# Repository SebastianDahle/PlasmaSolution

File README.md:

View this project on [CADLAB.io](https://cadlab.io/project/22637). 

# PlasmaSolution

The project *PlasmaSolution* is a Marie Sklodowoska Curie Actions - Individual Fellowship by the European Commission that aims to implement non-thermal plasma technology at the Department of Wood Science and Technology, Biotechnical Faculty, University of Ljubljana, Slovenia. Further goal of the project is the development and testing of plasma-cured coatings for wood protection as an innovative new appraoch in coatings deposition.

The equipment and methodology developed in the PlasmaSolution project shall be made openly available to everyone interested in reproducing or applying them. Participation in the activities and further developments are more than welcome! In case of questions and remarks, please contact Sebastian Dahle via [sebastian.dahle@bf.uni-lj.si](mailto:sebastian.dahle@bf.uni-lj.si).

## WARNING

**!! Dealing with plasma involves using high voltages. Please make sure you are familiar with all safety instructions and necessary practices!**

## Overview

A working plasma setup requires two essential parts:
* A [power supply](HV_power_supplies/) that delivers the required electrical energy, these are located at [HV_power_supplies/](HV_power_supplies/).
* A [plasma reactor](Plasma_devices/) as mechanical part, where the plasma is ignited, these are located at [Plasma_devices/](Plasma_devices/)

This repository currently includes constructions for both parts, that can be combined as indicated in the following table:

| | [Plasma_devices](Plasma_devices/) | adjustable Surface Barrier Discharge | mini-SBD | mini-DBD-Jet | Gliding-Arc-Jet *(long/short)* |
|-------------------------|---:|:---:|:---:|:---:|:--------------:|
| **[HV_power_supplies](HV_power_supplies/)** | | | |
|  Zero Voltage Switching |    |  X  |  X  |  X  |  X (long)      |
|  mini-Flyback *(AC/DC)* |    |  -  |  ?  |  AC |  AC/DC (short) |
|  Cockcroft-Walton       |    |  -  |  -  |  -  |  X (short)     |

## Getting Started

* [SolidWorks](https://www.solidworks.com/) - The CAD software used for mechanical constructions.
  * All constructions are provided openly accessible as STEP and PDF files.
  * Free software is available to view exported 3D STEP files, such as [STP Viewer](https://stpviewer.com/).
  * A free trial version of SolidWorks is available via their [website](https://www.solidworks.com/solution/job-functions/students).
* [KiCad EDA](kicad-pcb.org/download/) - Open source software used to develop circuits and PCB layouts.
  * All wiring plans are exported to PDF for easy access.
  * All PCB layouts are exported to Gerber format for easy ordering.
* [MS Visio](https://products.office.com/visio/) - The flow chart software for wiring plans.
  * All wiring plans are provided openly accessible as SVG and PDF files.
  * A free viewer for original proprietory files is availabe from [Microsoft](https://www.microsoft.com/download/details.aspx?id=35811).
* [MS Excel](https://products.office.com/excel/) - Used for tables and lists, whenever markdown files are less suited.
  * All charts, tables, and lists are exported as CSV and PDF.
* [MS Word](https://products.office.com/word/) - Used for instructions and publications, whenever markdown files are less suited.
  * All documents are exported to PDF.

## Contributing

Please read [CONTRIBUTING.md](https://github.com/SebastianDahle/PlasmaSolution/blob/master/CONTRIBUTING.md) for details on how to participate and the process for submitting pull requests to us, and check [CODE_OF_CONDUCT.md](https://github.com/SebastianDahle/PlasmaSolution/blob/master/CODE_OF_CONDUCT.md) for our code of conduct.

All releases are uploaded to Zenodo. 
* Latest release v1.0.0, see: 
* *Cite release as:* Sebastian Dahle. (2019, April 22). SebastianDahle/PlasmaSolution: First release (Version 1.0.0). Zenodo. http://doi.org/10.5281/zenodo.2648790

## Versioning

We use [SemVer](http://semver.org/) for versioning. For the versions available, see the [tags on this repository](https://github.com/SebastianDahle/PlasmaSolution/tags). 

## Authors

* **Billie Thompson** - *Initial work: README.md template* - [PurpleBooth](https://github.com/PurpleBooth)
* **Sebastian Dahle** - *Project coordinator & fellow PlasmaSolution* - [SebastianDahle](https://github.com/SebastianDahle)

See also the list of [contributors](https://github.com/SebastianDahle/PlasmaSolution/contributors) who participated in this project.

## License

This project is licensed under the GNU General Public License - see the [LICENSE.md](https://github.com/SebastianDahle/PlasmaSolution/blob/master/LICENSE) file for details

## Acknowledgments

* The project PlasmaSolution has received funding from the European Union's Horizon 2020 research and innovation programme under grant agreement No 745936.

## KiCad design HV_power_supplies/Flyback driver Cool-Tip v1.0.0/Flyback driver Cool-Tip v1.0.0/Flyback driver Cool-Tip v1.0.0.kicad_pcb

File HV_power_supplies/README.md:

# HV power supplies for plasma applications

## WARNING

**!! Manipulation of high voltages includes sincere health risks. Please make sure you are familiar with all safety instructions and necessary practices!**

## Overview

The following table provides an overview on the available constructions including basic properties:

| HV Power Supply        | Type | peak Voltage    | peak Power | Comments |
|------------------------|:----:|-----------------|-----------:|----------|
| Zero Voltage Switching |  AC  |  15 kV max      |  300 W max | USB+BT controlled; internal oscilloscope |
| mini-Flyback           |  AC  |  15 kV max      |   70 W max | Cheap & simple |
|                        |  DC  |  30 kV max      |   70 W max | Cheap & simple |
| Cockcroft-Walton       |  DC  | 2.8 kV / module |  500 W max | Easy scalable  |

## [Zero Voltage Switching](https://github.com/SebastianDahle/PlasmaSolution/tree/master/HV_power_supplies/ZVS-driver)

TODO

## [Mini-Flyback](https://github.com/SebastianDahle/PlasmaSolution/tree/master/HV_power_supplies/mini-Flyback)

*AC and DC version*

TODO

## [Cockcroft-Walton generator](https://github.com/SebastianDahle/PlasmaSolution/tree/master/HV_power_supplies/Cockcroft-Walton)

TODO

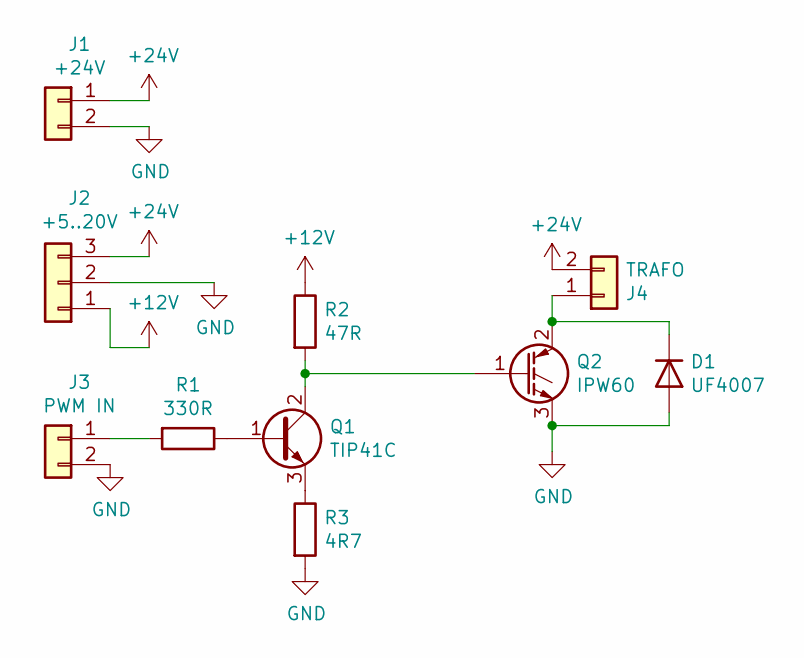
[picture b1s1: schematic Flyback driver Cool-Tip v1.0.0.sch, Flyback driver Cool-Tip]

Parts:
D1: UF4007; D_DO-201AD_P5.08mm_Vertical_AnodeUp
J1: +24V; TerminalBlock_Phoenix_MKDS-3-2-5.08_1x02_P5.08mm_Horizontal
J2: +5..20V; TerminalBlock_Phoenix_MKDS-1,5-3-5.08_1x03_P5.08mm_Horizont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
J3: PWM IN; TerminalBlock_Phoenix_MKDS-1,5-2-5.08_1x02_P5.08mm_Horizont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
J4: TRAFO; TerminalBlock_Phoenix_MKDS-3-2-5.08_1x02_P5.08mm_Horizontal
Q1: TIP41C; TO-220-3_Vertical
Q2: IPW60; TO-247-3_Vertical
R1: 330R; R_Axial_DIN0411_L9.9mm_D3.6mm_P12.70mm_Horizontal
R2: 47R; R_Axial_DIN0411_L9.9mm_D3.6mm_P12.70mm_Horizontal
R3: 4R7; R_Axial_DIN0411_L9.9mm_D3.6mm_P12.70mm_Horizontal

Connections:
+12V: J2.1, R2.1
+24V: J1.1, J2.3, J4.2
GND: D1.2 (A), J1.2, J2.2, J3.2, Q2.3 (E), R3.2
unnamed: D1.1 (K), J4.1, Q2.2 (C)
unnamed: J3.1, R1.2
unnamed: Q1.1 (B), R1.1
unnamed: Q1.2 (C), Q2.1 (G), R2.2
unnamed: Q1.3 (E), R3.1

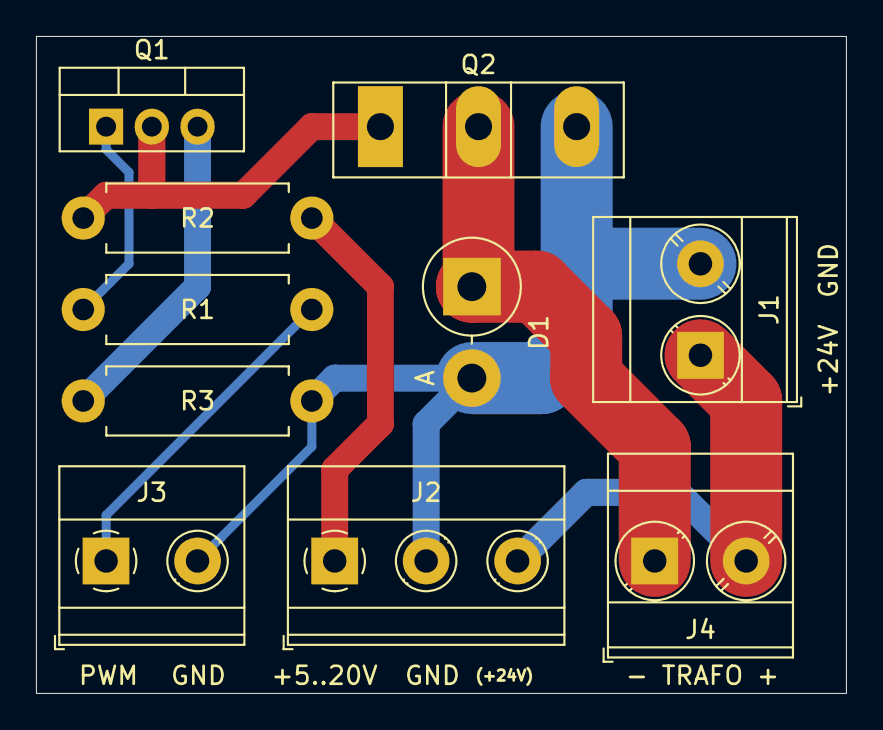
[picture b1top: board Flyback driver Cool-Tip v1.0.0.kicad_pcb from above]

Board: 2 copper layers, 45.0 x 36.5 mm, 10 parts (0 on the bottom side), 8 nets.

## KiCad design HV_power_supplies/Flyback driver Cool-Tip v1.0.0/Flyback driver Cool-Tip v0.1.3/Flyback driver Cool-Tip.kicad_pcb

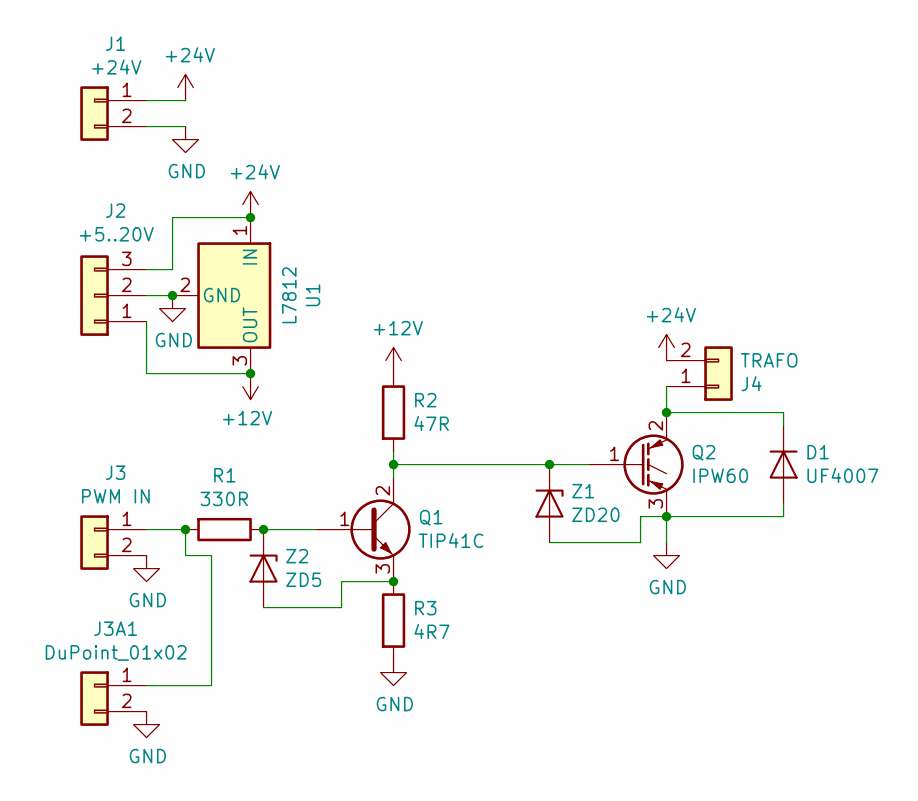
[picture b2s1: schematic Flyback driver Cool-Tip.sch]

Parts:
D1: UF4007; D_DO-201AD_P5.08mm_Vertical_AnodeUp
J1: +24V; TerminalBlock_Phoenix_MKDS-3-2-5.08_1x02_P5.08mm_Horizontal
J2: +5..20V; TerminalBlock_Phoenix_MKDS-1,5-3-5.08_1x03_P5.08mm_Horizont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
J3: PWM IN; TerminalBlock_Phoenix_MKDS-1,5-2-5.08_1x02_P5.08mm_Horizont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
J3A1: DuPoint_01x02; PinHeader_1x02_P2.54mm_Vertical
J4: TRAFO; TerminalBlock_Phoenix_MKDS-3-2-5.08_1x02_P5.08mm_Horizontal
Q1: TIP41C; TO-220-3_Vertical
Q2: IPW60; TO-247-3_Vertical
R1: 330R; R_Axial_DIN0411_L9.9mm_D3.6mm_P12.70mm_Horizontal
R2: 47R; R_Axial_DIN0411_L9.9mm_D3.6mm_P12.70mm_Horizontal
R3: 4R7; R_Axial_DIN0411_L9.9mm_D3.6mm_P12.70mm_Horizontal
U1: L7812; TO-220-3_Vertical
Z1: ZD20; D_DO-41_SOD81_P2.54mm_Vertical_KathodeUp
Z2: ZD5; D_DO-41_SOD81_P2.54mm_Vertical_KathodeUp

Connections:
+12V: J2.1, R2.1, U1.3 (OUT)
+24V: J1.1, J2.3, J4.2, U1.1 (IN)
GND: D1.2 (A), J1.2, J2.2, J3.2, J3A1.2, Q2.3 (E), R3.2, U1.2 (GND), Z1.2 (A)
unnamed: D1.1 (K), J4.1, Q2.2 (C)
unnamed: J3.1, J3A1.1, R1.2
unnamed: Q1.1 (B), R1.1, Z2.1 (K)
unnamed: Q1.2 (C), Q2.1 (G), R2.2, Z1.1 (K)
unnamed: Q1.3 (E), R3.1, Z2.2 (A)

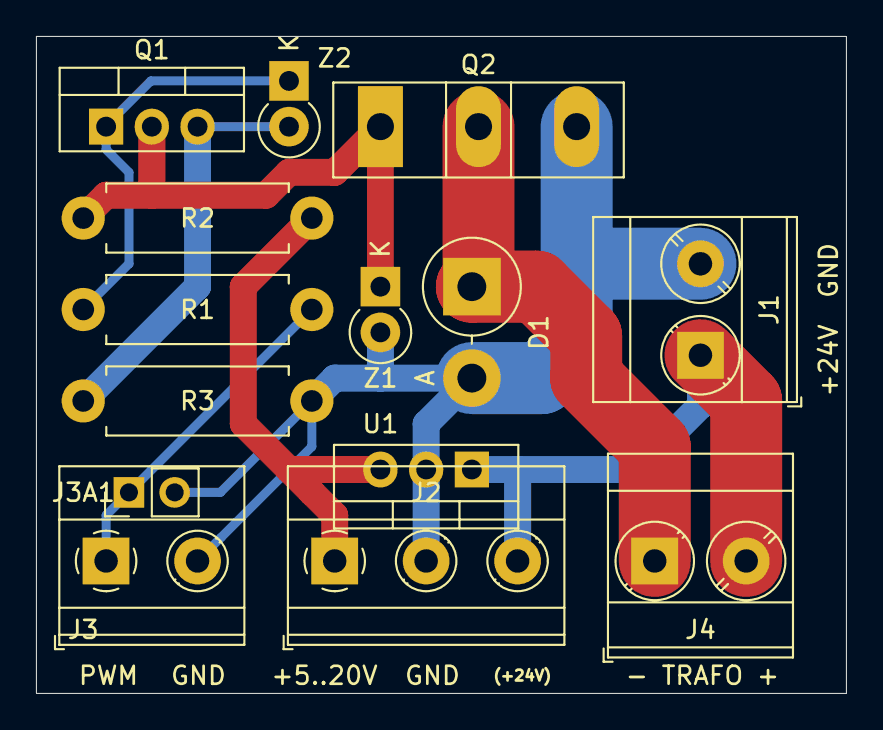
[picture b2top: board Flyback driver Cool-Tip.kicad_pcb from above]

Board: 2 copper layers, 45.0 x 36.5 mm, 14 parts (0 on the bottom side), 8 nets.

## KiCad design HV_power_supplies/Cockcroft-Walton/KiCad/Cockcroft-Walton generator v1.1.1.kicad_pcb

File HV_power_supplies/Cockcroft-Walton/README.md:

# Cockcroft-Walton generator Power Supply

This is a simple design of a direct current (DC) high voltage (HV) power supply. It is easy to scale, since it does not include an HV transformer. Instead, cascades of capacitors and diodes add up voltage according to the number of stages included.

## Getting started

* [**MANUAL.md**](https://github.com/SebastianDahle/PlasmaSolution/blob/master/HV_power_supplies/Cockcroft-Walton/MANUAL.md) - The manual provides a general overview on the device, it's working principle, and how to operate use it for plasma applications.
* [**BUILDING.md**](https://github.com/SebastianDahle/PlasmaSolution/blob/master/HV_power_supplies/Cockcroft-Walton/BUILDING.md) - The building instructions will walk you through the set up and advice you how to build one of these power supplies on your own.
* [**parts_list.md**](https://github.com/SebastianDahle/PlasmaSolution/blob/master/HV_power_supplies/Cockcroft-Walton/parts_list.md) - The parts list concisely presents all items that you need, along with a typical supplier and price.
* [*wiring/*](https://github.com/SebastianDahle/PlasmaSolution/tree/master/HV_power_supplies/Cockcroft-Walton/wiring) - The internal wiring and connections are presented in this sub-directory.
* [*housing/*](https://github.com/SebastianDahle/PlasmaSolution/tree/master/HV_power_supplies/Cockcroft-Walton/housing) - The construction of the housing and all related CAD files can be found in this sub-directory.

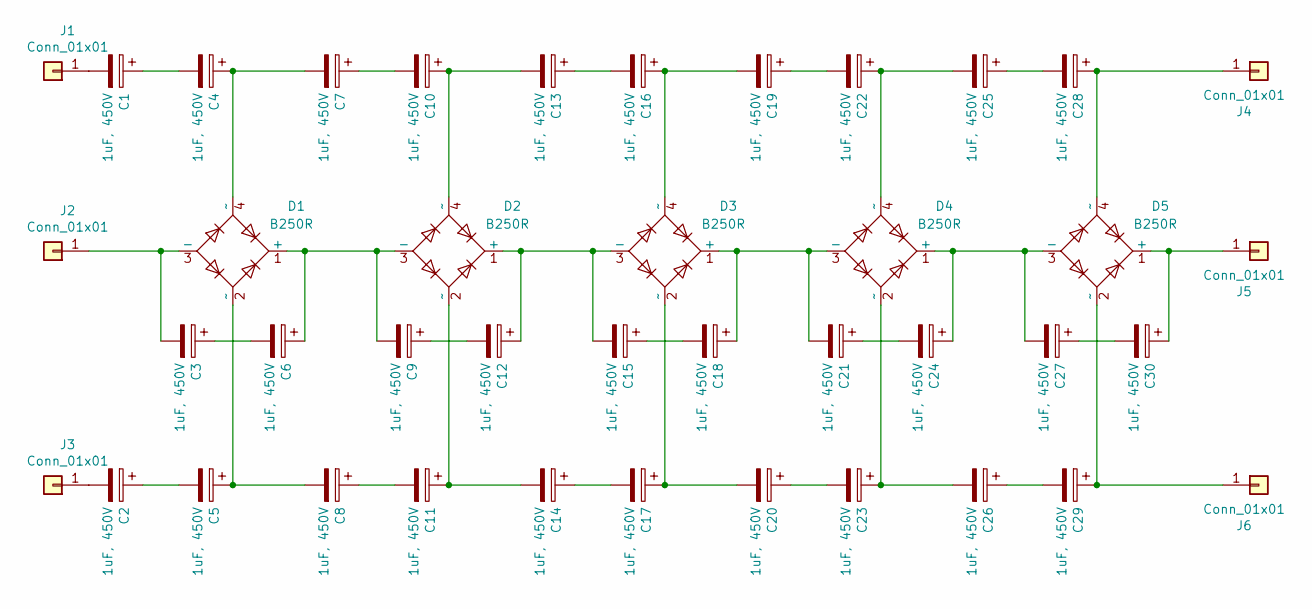
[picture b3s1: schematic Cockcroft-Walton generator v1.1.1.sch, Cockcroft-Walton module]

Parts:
C1, C2, C3, C4, C5, C6, C7, C8, C9, C10, C11, C12, C13, C14, C15, C16, C17, C18, C19, C20, C21, C22, C23, C24, C25, C26, C27, C28, C29, C30: 1uF, 450V; CP_Radial_D8.0mm_P2.50mm
D1, D2, D3, D4, D5: B250R; Diode_Bridge_Round_D9.0mm
J1, J2, J3, J4, J5, J6: Conn_01x01; Banana_Jack_1Pin

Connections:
unnamed: C1.1, C4.2
unnamed: C1.2, J1.1
unnamed: C2.1, C5.2
unnamed: C2.2, J3.1
unnamed: C3.1, C6.2
unnamed: C3.2, D1.3 (-), J2.1
unnamed: C4.1, C7.2, D1.4 (~~)
unnamed: C5.1, C8.2, D1.2 (~~)
unnamed: C6.1, C9.2, D1.1 (+), D2.3 (-)
unnamed: C10.1, C13.2, D2.4 (~~)
unnamed: C7.1, C10.2
unnamed: C11.1, C14.2, D2.2 (~~)
unnamed: C8.1, C11.2
unnamed: C12.1, C15.2, D2.1 (+), D3.3 (-)
unnamed: C9.1, C12.2
unnamed: C13.1, C16.2
unnamed: C14.1, C17.2
unnamed: C15.1, C18.2
unnamed: C16.1, C19.2, D3.4 (~~)
unnamed: C17.1, C20.2, D3.2 (~~)
unnamed: C18.1, C21.2, D3.1 (+), D4.3 (-)
unnamed: C19.1, C22.2
unnamed: C20.1, C23.2
unnamed: C21.1, C24.2
unnamed: C22.1, C25.2, D4.4 (~~)
unnamed: C23.1, C26.2, D4.2 (~~)
unnamed: C24.1, C27.2, D4.1 (+), D5.3 (-)
unnamed: C25.1, C28.2
unnamed: C26.1, C29.2
unnamed: C27.1, C30.2
unnamed: C28.1, D5.4 (~~), J4.1
unnamed: C29.1, D5.2 (~~), J6.1
unnamed: C30.1, D5.1 (+), J5.1

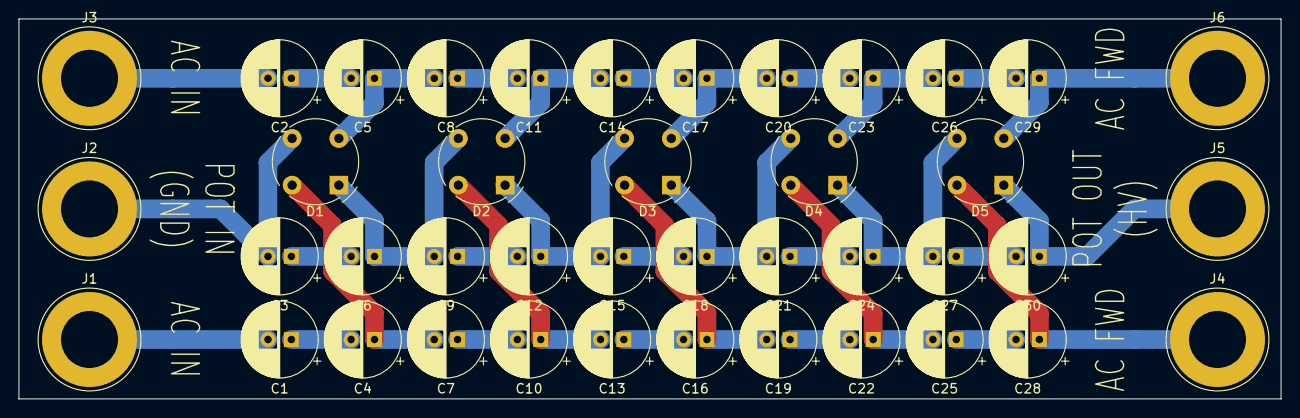
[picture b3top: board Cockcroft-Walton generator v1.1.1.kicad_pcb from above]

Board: 2 copper layers, 135.0 x 40.6 mm, 41 parts (0 on the bottom side), 33 nets.

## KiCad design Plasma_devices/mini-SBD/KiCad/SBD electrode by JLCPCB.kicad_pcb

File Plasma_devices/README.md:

# Plasma devices

## WARNING

**!! Operating plasma systems involves using high voltages. Please make sure you are familiar with all safety instructions and necessary practices!**

## Overview

The following table provides an overview on the available constructions including basic properties:

| Plasma device | type | treatment | Target applications |
|--------------------------------------|:----:|:--:|---------------------|
| adjustable Surface Barrier Discharge | SBD  | direct / diffusive | Smooth planar surfaces; Work pieces on conveyor belt |
| mini SBD                             | SBD  | direct / diffusive | Smooth planar surfaces; small lab-scale samples |
| mini DBD Jet                         | DBD  | remote / jet       | Localized treatments; Profiled surfaces; Plasma printing |
| Gliding Arc Jet                      | GA   | remote / jet       | Localized treatments; Profiled surfaces; Plasma printing |

## Adjustable Surface Barrier Discharge

TODO

## Mini SBD

TODO

## Mini DBD Jet

TODO

## Gliding Arc Jet

*long and short version*

TODO

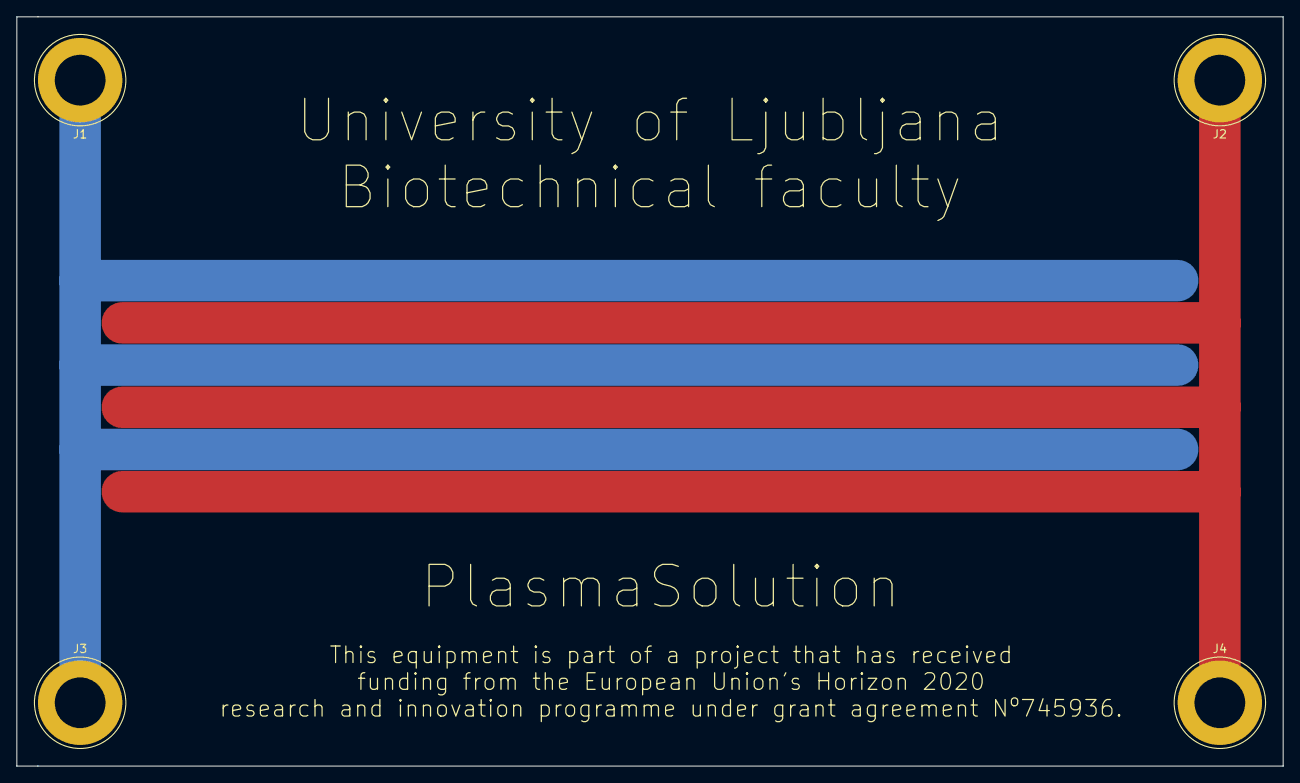
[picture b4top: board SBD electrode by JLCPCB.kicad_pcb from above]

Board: 2 copper layers, 152.4 x 90.2 mm, 4 parts (0 on the bottom side), 2 nets.

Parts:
J1, J2, J3, J4: Conn_01x01; Banana_Jack_1Pin

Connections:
unnamed: J1.1, J3.1
unnamed: J2.1, J4.1

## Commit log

2019-04-03 Create LICENSE
2019-04-22 Create contributors
2019-04-22 Rename contributors to contributors.md
2019-06-09 mv mini-Flyback_DC mini-Flyback
2019-06-09 completing previous commit
2019-06-09 mv CAD SolidWorks
2019-06-09 introduced sub-dirs HV_power_supplies & Plasma_devices
2019-06-22 Photos CW
2019-06-22 Photos ZVS
2019-12-31 Markdown pages for all power supplies included
2019-12-31 New devices
    Additional folders for most recent plasma devices added
2020-01-01 Some new images
2020-03-20 Backlink to CADLAB.io has been added.
2020-09-15 Plasma-CNC electrical added
2020-09-15 Updaged electrical
2020-09-15 ZVS circuit included
2020-09-15 DVS module included
2020-09-15 Components added
2020-09-15 CNC module included
2020-11-18 .
    .
